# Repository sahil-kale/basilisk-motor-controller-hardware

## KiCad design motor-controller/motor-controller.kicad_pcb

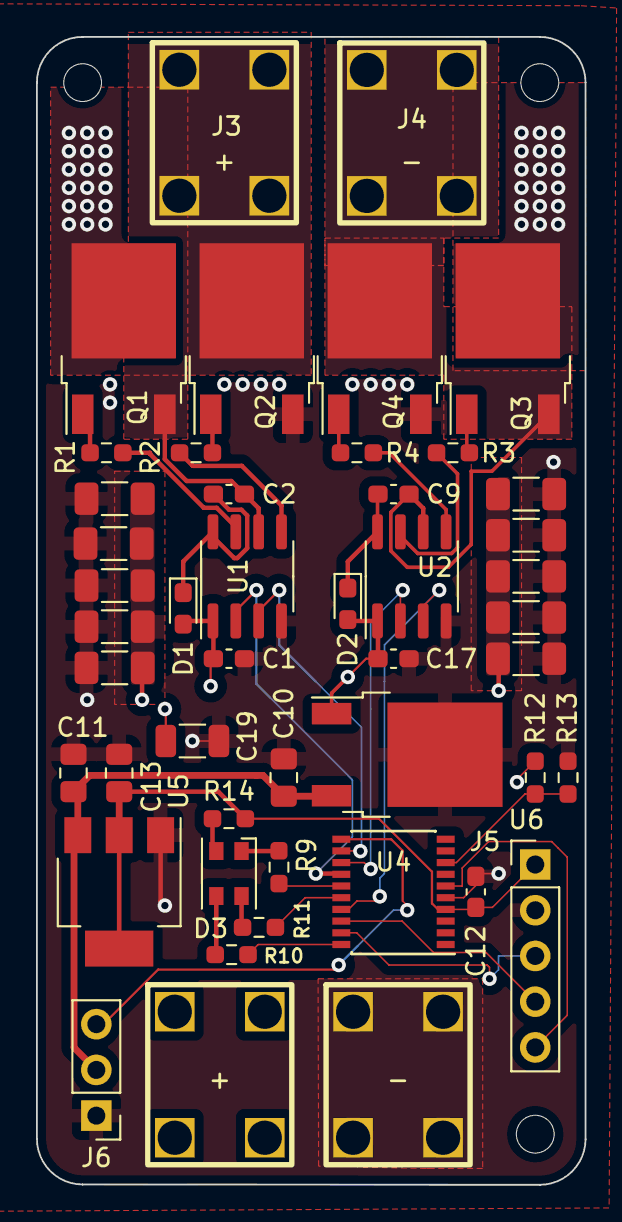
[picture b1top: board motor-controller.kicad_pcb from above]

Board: 4 copper layers, 30.5 x 63.8 mm, 51 parts (1 on the bottom side), 32 nets.

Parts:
C1, C2, C9, C12, C17: 0.1uF; C_0603_1608Metric_Pad1.08x0.95mm_HandSolder
C3, C4, C5, C6, C7, C8, C14, C15, C16, C18: 10uF; C_1206_3216Metric_Pad1.33x1.80mm_HandSolder
C10: 22uF; C_0805_2012Metric_Pad1.18x1.45mm_HandSolder
C11, C13: 10uF; C_0805_2012Metric_Pad1.18x1.45mm_HandSolder
C19: 10uF; C_1206_3216Metric
D1, D2: PMEG3005AESFYL; D_0603_1608Metric_Pad1.05x0.95mm_HandSolder
D3: CLV1A-FKB; LED_Cree-PLCC4_3.2x2.8mm_CCW
H1, H2, H3: 2mm; MountingHole_2.1mm
H5: Logo; basiliskLogo
J1, J3: SCREW +; 7698-SEMS
J2, J4: SCREW -; 7698-SEMS
J5: Conn_01x05; PinHeader_1x05_P2.54mm_Vertical
J6: Conn_01x03; PinHeader_1x03_P2.54mm_Vertical
Q1, Q2, Q3, Q4: AOD4132; TO-252-2
R1, R2, R3, R4: 4.7; R_0603_1608Metric_Pad0.98x0.95mm_HandSolder
R9, R10, R11: 470; R_0603_1608Metric_Pad0.98x0.95mm_HandSolder
R12: 8k; R_0603_1608Metric_Pad0.98x0.95mm_HandSolder
R13: 1k; R_0603_1608Metric_Pad0.98x0.95mm_HandSolder
R14: 0; R_0603_1608Metric_Pad0.98x0.95mm_HandSolder
U1, U2: IRS2301S; SOIC-8_3.9x4.9mm_P1.27mm
U4: STM32G030F6P6TR; SSOP-20_4.4x6.5mm_P0.65mm
U5: NCP1117ST33T3G; SOT-223
U6: LM78M05; TO-252-2

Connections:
+3V3: C12.1, C13.1, J5.1, R14.1, U4.4 (VDD/VDDA), U5.2 (OUT), U5.4 (OUT)
+5V: C10.1, C11.1, J6.2, U5.3 (IN), U6.3 (VO)
/SW_A: C2.2, J3.1, Q1.3 (S), Q2.2 (D), U1.6 (VS)
/SW_B: C9.2, J4.1, Q3.3 (S), Q4.2 (D), U2.6 (VS)
/controller/LED_B: R10.2, U4.20 (PB3/PB4/PB5/PB6)
/controller/LED_G: R11.2, U4.16 (PA11[PA9])
/controller/LED_R: R9.2, U4.15 (PB0/PB1/PB2/PA8)
/controller/NRST: J5.5, U4.6 (~RST)
/controller/PWM_IN: J6.3, U4.11 (PA4)
/controller/SWCLK: J5.3, U4.19 (PA15/PA14-BOOT0)
/controller/SWDIO: J5.4, U4.18 (PA13)
/controller/VBUS_SAMPLE: R12.2, R13.1, U4.8 (PA1)
GND: C1.2, C3.2, C4.2, C5.2, C6.2, C7.2, C8.2, C10.2, C11.2, C12.2, C13.2, C14.2, C15.2, C16.2, C17.2, C18.2, C19.2, J2.1, J5.2, J6.1, Q2.3 (S), Q4.3 (S), R13.2, U1.4 (COM), U2.4 (COM), U4.5 (VSS/VSSA), U5.1 (ADJ/GND), U6.2 (GND)
unnamed: C2.1, D1.1 (K), U1.8 (VB)
unnamed: C9.1, D2.1 (K), U2.8 (VB)
unnamed: D3.1 (RK), R9.1
unnamed: D3.2 (A), R14.2
unnamed: D3.3 (BK), R10.1
unnamed: D3.4 (GK), R11.1
unnamed: Q1.1 (G), R1.2
unnamed: Q2.1 (G), R2.2
unnamed: Q3.1 (G), R3.2
unnamed: Q4.1 (G), R4.2
unnamed: R1.1, U1.7 (HO)
unnamed: R2.1, U1.5 (LO)
unnamed: R3.1, U2.7 (HO)
unnamed: R4.1, U2.5 (LO)
PWM_A_HIGH: U1.2 (HIN), U4.14 (PA7)
PWM_A_LOW: U1.3 (LIN), U4.12 (PA5)
PWM_B_HIGH: U2.2 (HIN), U4.13 (PA6)
PWM_B_LOW: U2.3 (LIN), U4.17 (PA12[PA10])
VBUS: C1.1, C3.1, C4.1, C5.1, C6.1, C7.1, C8.1, C14.1, C15.1, C16.1, C17.1, C18.1, C19.1, D1.2 (A), D2.2 (A), J1.1, Q1.2 (D), Q3.2 (D), R12.1, U1.1 (VCC), U2.1 (VCC), U6.1 (VI)

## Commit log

2021-12-30 Inital Commit and H-Bridge stuff
2021-12-31 Add in a lot of other stuff hehe
2022-01-02 Remove MCU stuff
2022-01-05 MCU Upload
2022-01-05 Minor schematic changes
2022-01-05 Test Commit
2022-01-09 Update fp-info-cache
2022-01-10 Add in some more footprints and components
2022-01-15 Added SEMS footprint
2022-01-15 first stab at placement
2022-01-15 More layout stuff
2022-01-29 Stuff
2022-01-29 Minor trace change and add STEP file
2022-02-13 FInish layout
2022-02-13 Random stuff
2022-02-24 Add in released stuff
2022-04-01 Update hardware
